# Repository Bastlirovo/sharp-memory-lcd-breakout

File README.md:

# sharp-memory-lcd-breakout
Breakout Board for Sharp Memory LCD 2.7", two options for 5V StepUp

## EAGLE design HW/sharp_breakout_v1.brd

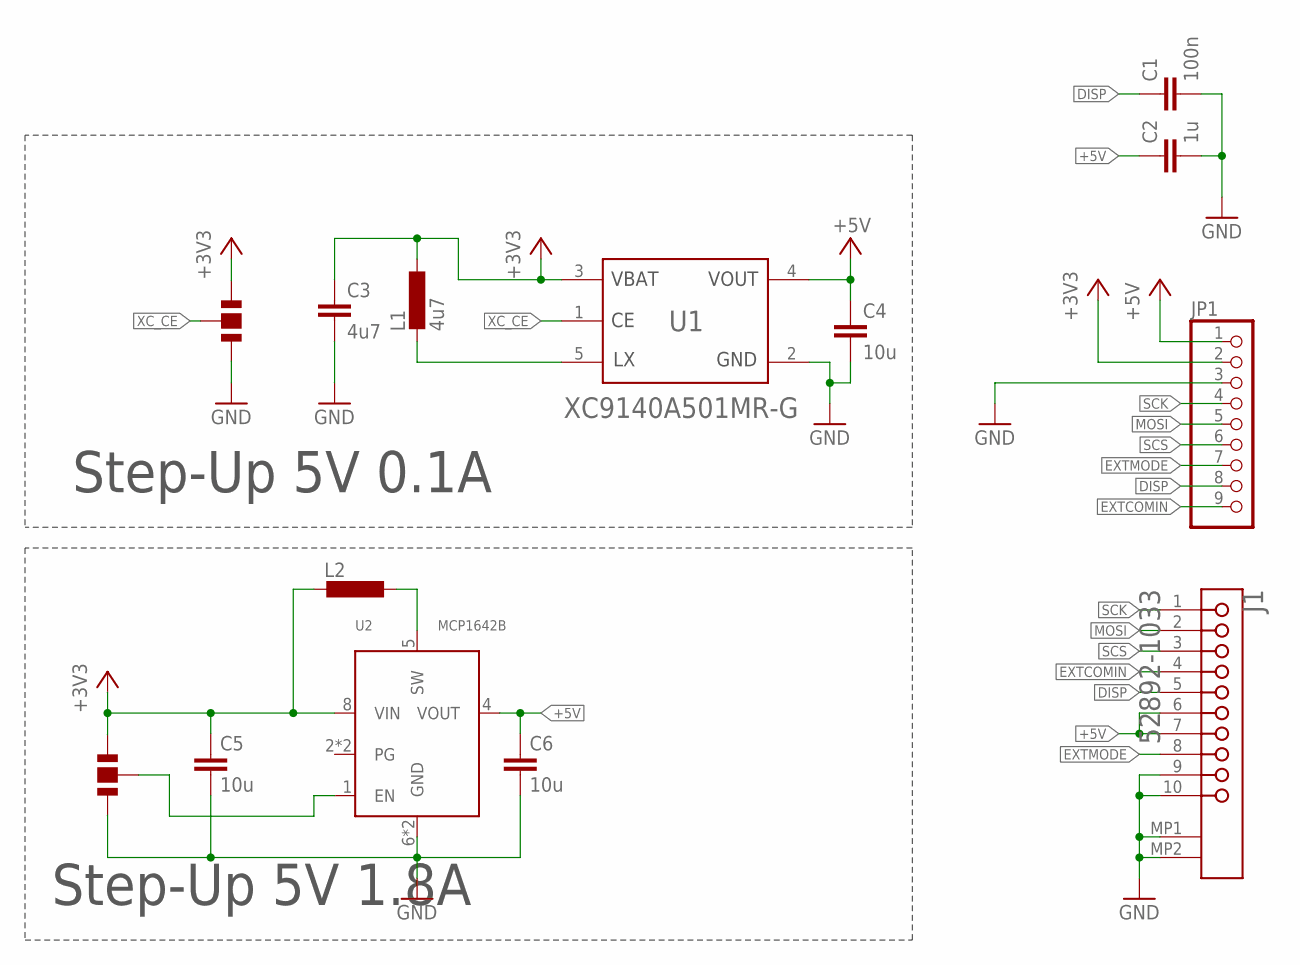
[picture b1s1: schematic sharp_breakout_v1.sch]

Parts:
C1: 100n; C0603K
C2: 1u; C0603K
C3: 4u7; C0603K
C4: 10u; C0603K
C5, C6: 10u; C1206
J1: MOLEX_52892-1033MOLEX_52892-1033_0_0; MOLEX_52892-1033_0
JP1: PINHD-1X9; 1X09
L1: 4u7; L3225M
L2: L-EUL4532P; L4532P
U1: TOREX_XC9140A501MR-GTOREX_XC9140A501MR-G_0_0; TOREX_XC9140A501MR-G_0
U2: MCP1642B; MSOP8
U$1, U$7: JUMPER; 2-WAY

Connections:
+3V3: C3.1, C5.1, JP1.2, L1.1, L2.2, U1.3 (VBAT), U2.8 (VIN), U$1.P$3, U$7.P$2
+5V: C2.1, C4.1, C6.1, J1.6, J1.7, JP1.1, U1.4 (VOUT), U2.4 (VOUT)
DISP: C1.1, J1.5, JP1.8
EXTCOMIN: J1.4, JP1.9
EXTMODE: J1.8, JP1.7
GND: C1.2, C2.2, C3.2, C4.2, C5.2, C6.2, J1.9, J1.10, J1.MP1, J1.MP2, JP1.3, U1.2 (GND), U2.6 (GND), U2.7 (GND), U$1.P$2, U$7.P$3
MOSI: J1.2, JP1.5
unnamed: L1.2, U1.5 (LX)
unnamed: L2.1, U2.5 (SW)
unnamed: U2.1 (EN), U$7.P$1
SCK: J1.1, JP1.4
SCS: J1.3, JP1.6
XC_CE: U1.1 (CE), U$1.P$1

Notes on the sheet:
Step-Up 5V 1.8A
Step-Up 5V 0.1A

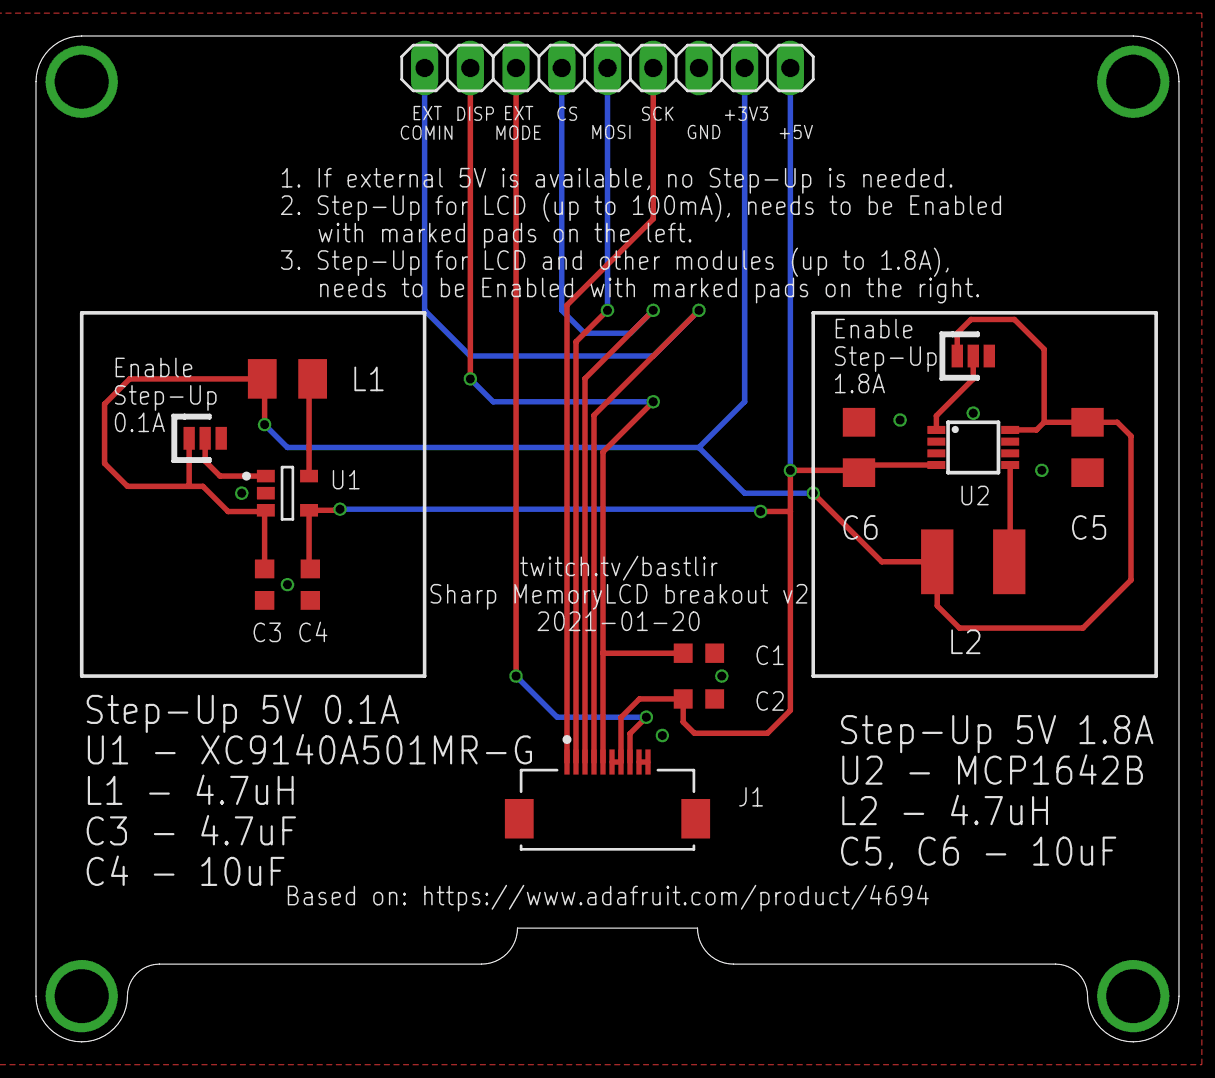
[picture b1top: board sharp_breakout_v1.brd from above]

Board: 2 copper layers, 63.5 x 55.9 mm, 14 parts (0 on the bottom side), 13 nets.

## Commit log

2021-01-21 Initial commit of HW v1
